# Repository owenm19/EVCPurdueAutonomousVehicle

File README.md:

The new home for Purdue EVC Autonomous Division.

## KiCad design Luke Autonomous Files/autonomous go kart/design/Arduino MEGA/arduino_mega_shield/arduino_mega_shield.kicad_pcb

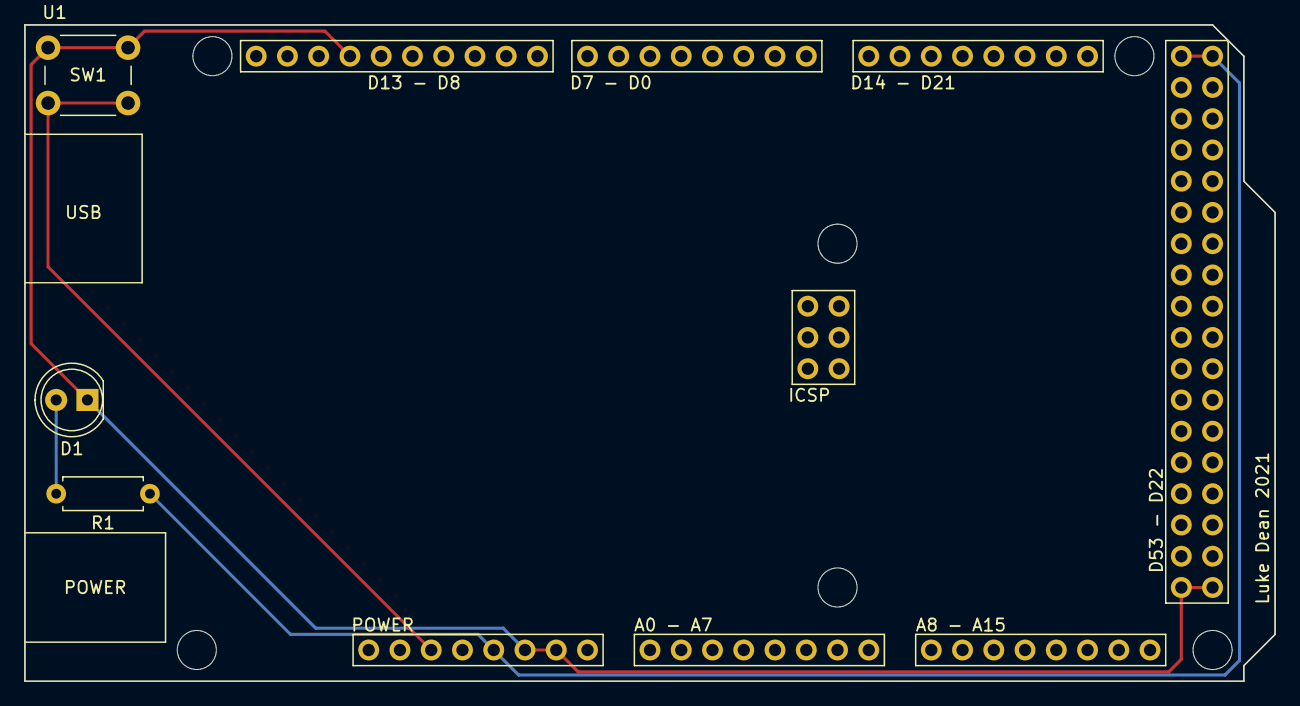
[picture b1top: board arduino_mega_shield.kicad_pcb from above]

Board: 2 copper layers, 101.6 x 53.3 mm, 4 parts (0 on the bottom side), 4 nets.

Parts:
D1: LED; LED_D5.0mm
R1: R; R_Axial_DIN0207_L6.3mm_D2.5mm_P7.62mm_Horizontal
SW1: SW_Push; SW_PUSH_6mm
U1: basic_shield

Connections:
+5V: R1.1, U1.4, U1.50, U1.51
GND: D1.1, SW1.2, U1.5, U1.6, U1.27, U1.84, U1.85
unnamed: D1.2, R1.2
unnamed: SW1.1, U1.2

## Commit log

2023-01-21 All Luke Dean's Embedded Systems Stuff
    This is the Embedded Systems Stuff
2023-01-21 PWM to analog Stuff
2023-02-11 UART Auto Code for Arduino
